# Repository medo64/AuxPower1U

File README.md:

# AuxPower1U

This project is 1U enclosed case with 5 DC outputs that are separately
controllable via front momentary switches with LEDs.

Features:
* 5 DC inputs (input 1 has to be 9-15V)
* 5 DC outputs
* 5 separate button controls
* voltage and current monitoring (9-60V, 0-8A, per channel)
* temperature monitoring
* OLED output
* 3 power supplies
* 2 power inputs (one for UPS, one for non-UPS)

## Usage

Different functionality can be triggered by different key press lengths:
* <5 seconds:    detail mode for channel (turns off automatically in 60 seconds)
* 5-10 seconds:  reset once button is released (or turns on if output was turned off)
* 10-13 seconds: turn off output permanently
* >13 seconds:   ignore press

## Uart Communication

Current usage will be written to UART twice a second. See example below:

    1: 11.98V 0.40A   4.77W [ON]
    2: 15.40V 3.10A  47.74W [ON]
    3: 15.42V 0.00A   0.00W [OFF]
    4: 15.42V 0.00A   0.00W [OFF]
    5: 54.13V 0.00A   0.00W [OFF]
    T: 23.4C

Each line consists of the space-separated readings. If line starts with a
channel number (1-5), what follows will be readings for the given channel of
voltage (V), current (A), and power (W) followed by a channel status. If line
starts with a letter T, what follows is a temperature. Each line will end with
`CRLF`.

Commands can be given to device by sending command code followed by a channel.
Available commands are:
* `D`: Disable
* `E`: Enable
* `R`: Reset
* `I`: Information

For example, to disable channel 2 use:

    D2

### 3.5mm Uart Connector

This is pinout, as viewed from board side (i.e. as marked on board).

| JST | 3.5mm  | Signal |
|-----|--------|--------|
|  1  | Tip    | RX     |
|  2  | Sleeve | GND    |
|  3  | Ring   | TX     |

## Test Mode

To enter test mode, keep buttons 1 and 5 pressed while powering board on. Each
subsequent press will then cycle through channel and show voltage/current values
in higher than normal resolution.

## Components

* [MainController](src/MainController/README.md): Allowing for monitoring and resetting of lines
* [AuxFanController](https://github.com/medo64/AuxFanController): Optional board to run PWM fans dependant on temperature
* [DellPowerTrigger](https://github.com/medo64/DellPowerTrigger): Emulating Dell charger for 5.5x2.1mm input

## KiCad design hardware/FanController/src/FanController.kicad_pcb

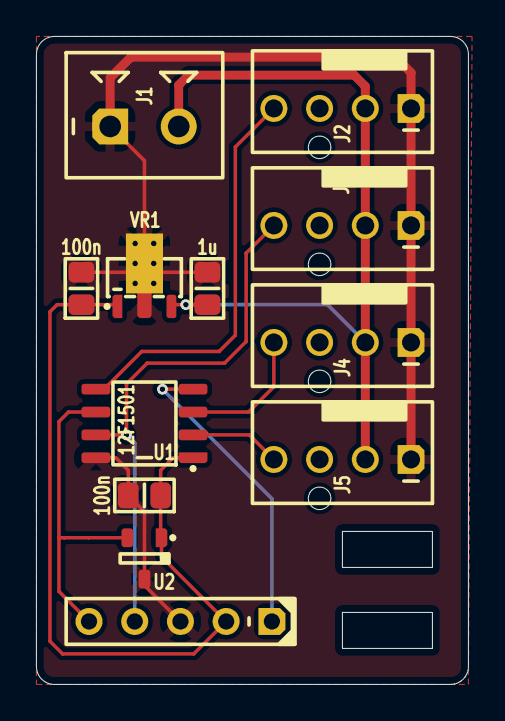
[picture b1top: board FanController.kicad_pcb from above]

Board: 2 copper layers, 24.0 x 36.0 mm, 12 parts (0 on the bottom side), 9 nets.

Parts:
C1, C2: 100n; C (0805)
C3: 1u; C (0805)
ICSP: Microchip PIC; ICSP PIC Pogo (5w)
J1: MC 1,5/2; J Phoenix MCV (2w)
J2, J3, J4, J5: Fan; J Molex 047053 [Fan] (4w)
U1: 12F1501; U Micro [PIC12F1501] (SOIC-8)
U2: MCP9701A; U Temperature Analog [MCP9701] (SOT23-3)
VR1: AS78L05RTR; VR Linear 5V 100mA [AS78L05RTR-E1] (SOT89-3')

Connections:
+5V: C1.1, C2.1, ICSP.2, U1.1, U2.1, VR1.1
+12V: C3.1, J1.2, J2.2, J3.2, J4.2, J5.2, VR1.3
ADC_TEMPERATURE: ICSP.5, U1.6, U2.2
GND: C1.2, C2.2, C3.2, ICSP.3, J1.1, J2.1, J3.1, J4.1, J5.1, U1.8, U2.3, VR1.2
ICSP_VPP: ICSP.1, U1.4
OUT_PWM1: J2.4, U1.5
OUT_PWM2: ICSP.4, J3.4, U1.7
OUT_PWM3: J4.4, U1.3
OUT_PWM4: J5.4, U1.2

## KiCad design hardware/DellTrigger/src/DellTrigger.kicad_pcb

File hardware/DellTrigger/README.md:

# DellTrigger

Small board that allows standard 5.5x2.1 power supply to be used for Dell
Optiplex 3050 Micro.

For the purpose of powering Dell 3050 Micro, one needs to trick computer to
recognize charger correctly. For that purpose, [a simple circuit](https://forum.arcadecontrols.com/index.php?topic=118584.0)
is needed.

Features:
* Allows 5.5x2.1mm DC input
* Has 1-wire control chip (DS2501)
* Dell-compatible 3-pin output

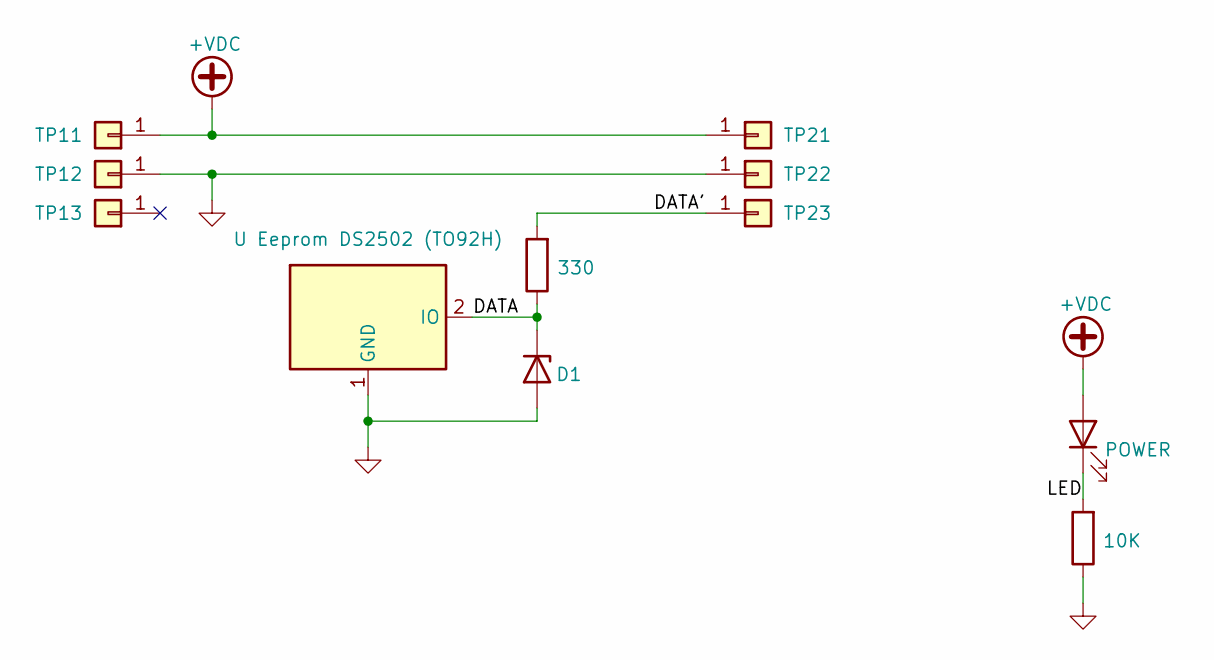
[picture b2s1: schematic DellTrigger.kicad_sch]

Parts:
D1: CUS08F30; D (SOD323)
DS1: POWER; DS (0805)
R1: 330; R (0805)
R2: 10K; R (0805)
TP11, TP21: +; TP Pad (8.0x4.0)
TP12, TP22: -; TP Pad (8.0x4.0)
TP13: S; TP Pad (8.0x4.0)
TP23: D; TP Pad (8.0x4.0)
U1: U Eeprom DS2502 (TO92H)

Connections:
+VDC: DS1.2 (A), TP11.1, TP21.1
DATA: D1.1 (K), R1.1, U1.2 (IO)
DATA': R1.2, TP23.1
GND: D1.2 (A), R2.1, TP12.1, TP22.1, U1.1 (GND)
LED: DS1.1 (K), R2.2

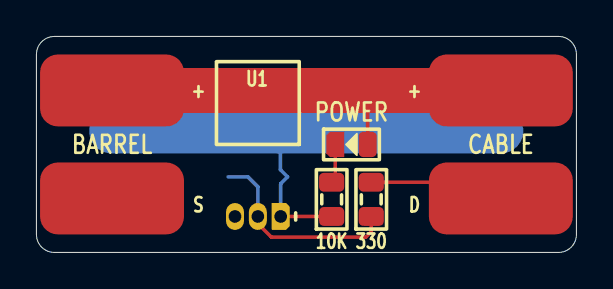
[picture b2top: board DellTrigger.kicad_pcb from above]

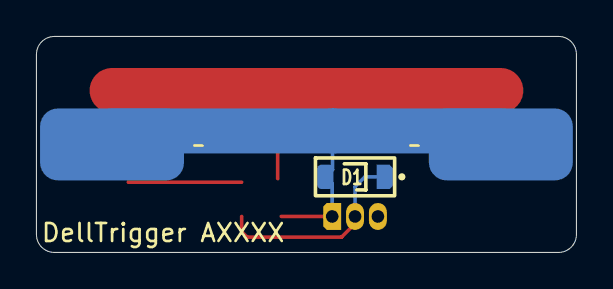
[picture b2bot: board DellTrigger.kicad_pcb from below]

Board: 2 copper layers, 30.0 x 12.0 mm, 11 parts (3 on the bottom side), 5 nets.

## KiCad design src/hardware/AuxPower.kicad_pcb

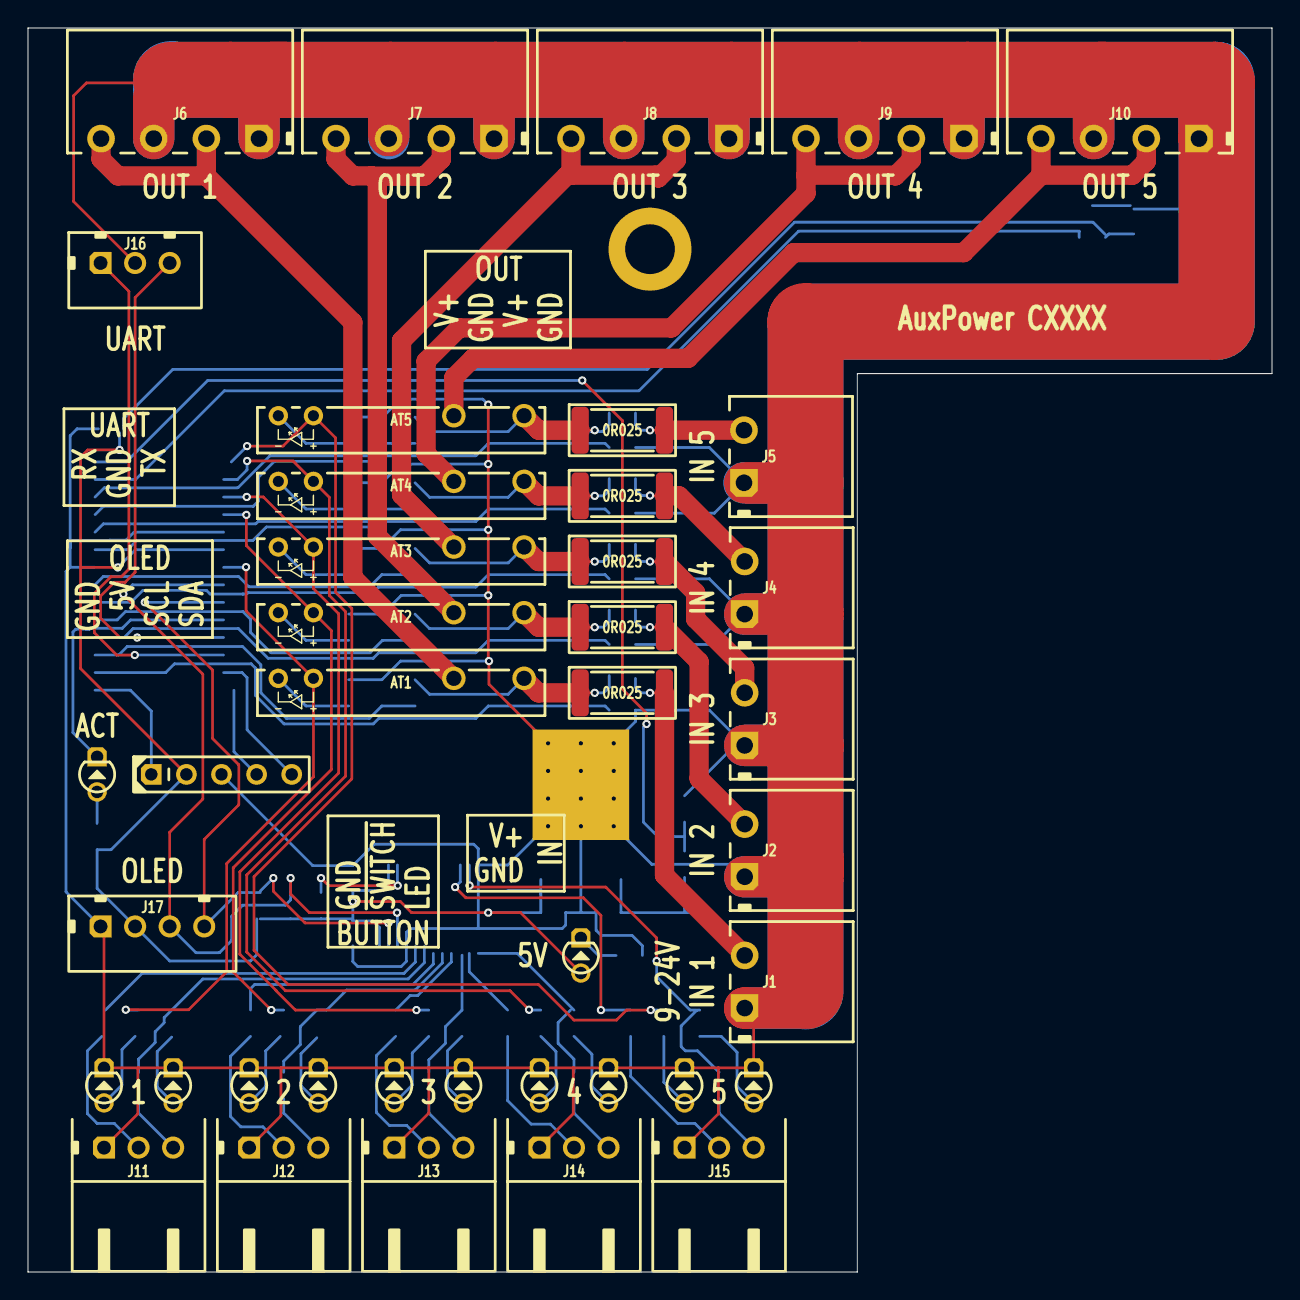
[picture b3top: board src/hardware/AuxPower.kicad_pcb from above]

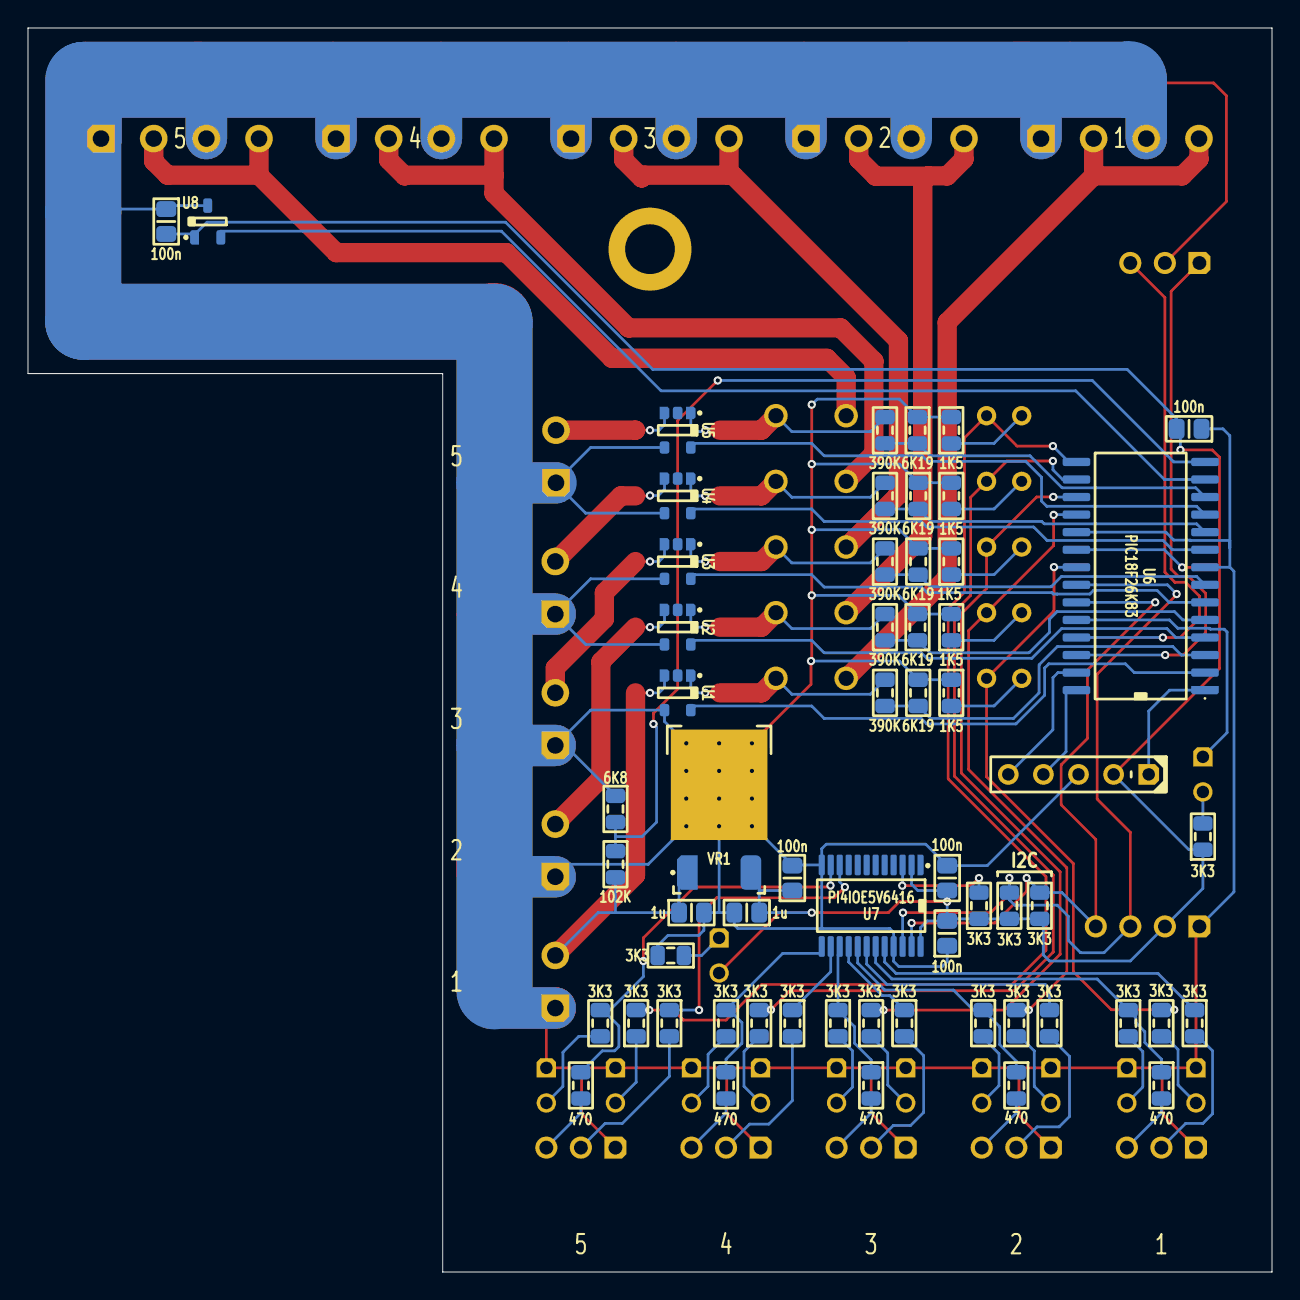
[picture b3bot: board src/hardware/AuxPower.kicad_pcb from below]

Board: 2 copper layers, 90.0 x 90.0 mm, 99 parts (58 on the bottom side), 80 nets.

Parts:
AT1, AT2, AT3, AT4, AT5: AQZ202G; AT PhotoMOS [AQZ202G] (SIP-4)
C1, C2, C3, C4, C5: 100n; C (0805)
C6, C7: 1u; C (0805)
DS1, DS2, DS3, DS4, DS5, DS6, DS7, DS8, DS9, DS10, DS11, DS12: LED; DS (D3.0)
ICSP: Microchip PIC; ICSP PIC Pogo DS (5w)
J1, J2, J3, J4, J5: MC 1,5/2; J Phoenix MC (2w)
J6, J7, J8, J9, J10: MC 1,5/4; J Phoenix MC (4w)
J11, J12, J13, J14, J15: S3B-XH-A; J JST XH S (3w)
J16: B3B-XH-A; J JST XH B [UART] (3w)
J17: B4B-XH-A; J JST XH B [I2C] (4w)
MH1: M3; MH M3
R1, R2, R3, R4, R5: 0R025; R (2512)
R6, R7, R8, R9, R10: 470; R (0805)
R11, R12, R13, R14, R15: 1K5; R (0805)
R16, R17, R18, R19, R20, R21, R22, R23, R24, R25, R26, R27, R28, R29, R30, R31, R32, R33, R34, R35: 3K3; R (0805)
R36, R37, R38, R39, R40: 6K19; R (0805)
R41: 6K8; R (0805)
R42: 102K; R (0805)
R43, R44, R45, R46, R47: 390K; R (0805)
U1, U2, U3, U4, U5: HV7801; U CurrentMonitor [HV7801] (SOT23-5)
U6: PIC18F26K83; U Micro [PIC18F26K83] (SOIC-28)
U7: PI4IOE5V6416; U Expander I2C [PI4IOE5V6416LEX] (TSSOP-24)
U8: MCP9701; U Temperature Analog [MCP9701] (SOT23-3)
VR1: AS7805ADTR; VR Linear 5V 1000mA [AS7805ADTR-G1] (TO252-2')

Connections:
5V: C1.2, C2.1, C3.1, C4.1, C5.1, C6.2, DS11.2, ICSP.2, J17.2, R16.2, R27.2, R34.2, R35.2, U6.20, U7.2, U7.24, U8.1, VR1.3
ADC_CURRENT1: U1.5, U6.2
ADC_CURRENT2: U2.5, U6.4
ADC_CURRENT3: U3.5, U6.6
ADC_CURRENT4: U4.5, U6.9
ADC_CURRENT5: U5.5, U6.11
ADC_TEMPERATURE: U6.13, U8.2
ADC_VOLTAGE1: R36.1, R43.1, U6.3
ADC_VOLTAGE2: R37.1, R44.2, U6.5
ADC_VOLTAGE3: R38.1, R45.2, U6.7
ADC_VOLTAGE4: R39.1, R46.2, U6.10
ADC_VOLTAGE5: R40.1, R47.2, U6.12
ADC_VOLTAGE_IN: R41.1, R42.2, U6.14
BUTTON1_LED: J11.3, R6.1
BUTTON1_SWITCH: J11.2, R29.1
BUTTON2_LED: J12.3, R7.1
BUTTON2_SWITCH: J12.2, R30.1
BUTTON3_LED: J13.3, R8.1
BUTTON3_SWITCH: J13.2, R31.1
BUTTON4_LED: J14.3, R9.1
BUTTON4_SWITCH: J14.2, R32.1
BUTTON5_LED: J15.3, R10.1
BUTTON5_SWITCH: J15.2, R33.1
EXPANDER_RESET: R16.1, U7.3
GND: C1.1, C2.2, C3.2, C4.2, C5.2, C6.1, C7.1, DS1.1, DS2.1, DS3.1, DS4.1, DS5.1, DS6.1, DS7.1, DS8.1, DS9.1, DS10.1, ICSP.3, J1.1, J2.1, J3.1, J4.1, J5.1, J6.1, J6.3, J7.1, J7.3, J8.1, J8.3, J9.1, J9.3, J10.1, J10.3, J11.1, J12.1, J13.1, J14.1, J15.1, J16.2, J17.1, R11.2, R12.1, R13.1, R14.1, R15.1, R26.1, R36.2, R37.2, R38.2, R39.2, R40.2, R41.2, U1.4, U2.4, U3.4, U4.4, U5.4, U6.8, U6.19, U7.12, U7.21, U8.3, VR1.2
I2C_SCL: J17.3, R35.1, U6.22, U7.22
I2C_SDA: J17.4, R34.1, U6.23, U7.23
ICSP_CLK: ICSP.5, U6.27
ICSP_DAT: ICSP.4, U6.28
ICSP_VPP: ICSP.1, U6.1
INPUT1: C7.2, J1.2, R1.1, R42.1, U1.3, VR1.1
INPUT1': AT1.4, R1.2, R43.2, U1.1
INPUT2: J2.2, R2.1, U2.3
INPUT2': AT2.4, R2.2, R44.1, U2.1
INPUT3: J3.2, R3.1, U3.3
INPUT3': AT3.4, R3.2, R45.1, U3.1
INPUT4: J4.2, R4.1, U4.3
INPUT4': AT4.4, R4.2, R46.1, U4.1
INPUT5: J5.2, R5.1, U5.3
INPUT5': AT5.4, R5.2, R47.1, U5.1
IN_BUTTON1_SWITCH: R29.2, U7.20
IN_BUTTON2_SWITCH: R30.2, U7.18
IN_BUTTON3_SWITCH: R31.2, U7.16
IN_BUTTON4_SWITCH: R32.2, U7.14
IN_BUTTON5_SWITCH: R33.2, U7.10
LED_ACTIVITY: DS12.2, R27.1
LED_BUTTON_INT_1: DS1.2, R28.1
LED_BUTTON_INT_2: DS2.2, R22.1
LED_BUTTON_INT_3: DS3.2, R23.1
LED_BUTTON_INT_4: DS4.2, R24.1
LED_BUTTON_INT_5: DS5.2, R25.1
LED_OUTPUT1: DS6.2, R17.2
LED_OUTPUT2: DS7.2, R18.2
LED_OUTPUT3: DS8.2, R19.2
LED_OUTPUT4: DS9.2, R20.2
LED_OUTPUT5: DS10.2, R21.2
LED_POWER: DS11.1, R26.2
OUTPUT1: AT1.3, J6.2, J6.4
OUTPUT2: AT2.3, J7.2, J7.4
OUTPUT3: AT3.3, J8.2, J8.4
OUTPUT4: AT4.3, J9.2, J9.4
OUTPUT5: AT5.3, J10.2, J10.4
OUT_ACTIVITY: DS12.1, U6.24
OUT_BUTTON1_LED: R6.2, R28.2, U7.19
OUT_BUTTON2_LED: R7.2, R22.2, U7.17
OUT_BUTTON3_LED: R8.2, R23.2, U7.15
OUT_BUTTON4_LED: R9.2, R24.2, U7.13
OUT_BUTTON5_LED: R10.2, R25.2, U7.11
OUT_OUTPUT1: AT1.2, R17.1, U6.21
OUT_OUTPUT1': AT1.1, R11.1
OUT_OUTPUT2: AT2.2, R18.1, U6.18
OUT_OUTPUT2': AT2.1, R12.2
OUT_OUTPUT3: AT3.2, R19.1, U6.17
OUT_OUTPUT3': AT3.1, R13.2
OUT_OUTPUT4: AT4.2, R20.1, U6.16
OUT_OUTPUT4': AT4.1, R14.2
OUT_OUTPUT5: AT5.2, R21.1, U6.15
OUT_OUTPUT5': AT5.1, R15.2
UART_RX: J16.1, U6.26
UART_TX: J16.3, U6.25

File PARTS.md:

## AuxPower PCB

### Properties

|      |                            |
|------|----------------------------|
| Size | 90.0 x 90.0 mm ~ 15.2 sqin |


### Parts

|  # | Part name                                          | RefDes   | Source                                                      |
|---:|----------------------------------------------------|----------|-------------------------------------------------------------|
|  5 | AT PhotoMOS 6A 60V [AQZ202G] (SIP-4)               | AT1-AT5  | 255-5699-ND                                                 |
|  5 | C 100nF X7R 50V (0805)                             | C1-c5    | 478-5311-1-ND                                               |
|  2 | C 1uF X7R 25V (0805)                               | C6-C7    | 1276-1066-1-ND                                              |
| 12 | DS LED Red (3mm)                                   | DS1-DS12 | 754-1218-ND                                                 |
|  5 | J Phoenix MC 1,5/ 2-G-3,81 R/A (2w)                | J1-J5    | ED2808-ND                                                   |
|  5 | J Phoenix MC 1,5/ 4-G-3,81 R/A (4w)                | J6-J10   | ED2810-ND                                                   |
|  5 | J JST XH r/a (3w)                                  | J11-J15  | 455-S3B-XH-A-ND                                             |
|  1 | J JST XH (3w)                                      | J16      | 455-2248-ND                                                 |
|  1 | J JST XH (4w)                                      | J17      | 455-B4B-XH-A-ND                                             |
|  5 | R 0.025 1% 3W (2512)                               | R1-R5    | CRA2512-FZ-R025ELFCT-ND                                     |
|  5 | R 470 1% 0.125W (0805)                             | R6-R10   | RMCF0805FT470RCT-ND                                         |
|  5 | R 1.5K 1% 0.125W (0805)                            | R11-R15  | RMCF0805FT1K50CT-ND                                         |
| 20 | R 3.3K 1% 0.125W (0805)                            | R16-R35  | RMCF0805FT3K30CT-ND                                         |
|  5 | R 6.19K 0.1% 0.125W (0805)                         | R36-R40  | P6.19KDACT-ND                                               |
|  1 | R 6.80K 0.1% 0.125W (0805)                         | R41      | P6.8KDACT-ND                                                |
|  1 | R 102K 0.1% 0.125W 1% (0805)                       | R42      | P102KDACT-ND                                                |
|  5 | R 390K 0.1% 0.125W (0805)                          | R43-R47  | P390KDACT-ND                                                |
|  5 | U CurrentMonitor [HV7801] (SOT23-5)                | U1-U5    | HV7801K1-GCT-ND                                             |
|  1 | U Micro [PIC18F26K83] (SOIC-28)                    | U6       | PIC18F26K83-I/SO-ND                                         |
|  1 | U Expander I2C [PI4IOE5V6416LEX] (TSSOP-24)        | U7       | PI4IOE5V6416LEXDICT-ND                                      |
|  1 | U Temperature Analog 2% [MCP9701A] (SOT23-3)       | U8       | MCP9701AT-E/TTCT-ND                                         |
|  1 | VR Linear 5V 1A [AS7805ADTR-G1] (TO252-2)          | VR1      | AS7805ADTR-G1DICT-ND                                        |
|  5 | P Phoenix MC 1,5/ 2-ST-3,81 (2w)                   | P1-P5    | ED2875-ND                                                   |
|  5 | P Phoenix MC 1,5/ 4-ST-3,81 (4w)                   | P6-P10   | ED2877-ND                                                   |


### Pin Usage (PIC18F26K83)

|  # | Pin | ICSP | Function | Description                                |
|---:|:---:|------|----------|--------------------------------------------|
|  1 | RE3 | MCLR |          |                                            |
|  2 | RA0 |      | ANA0     | Out 1: Current (ADC 1.024V 1:5)            |
|  3 | RA1 |      | ANA1     | Out 1: Voltage (ADC 1.024V 16mV/bit; 1:64) |
|  4 | RA2 |      | ANA2     | Out 2: Current (ADC 1.024V 1:5)            |
|  5 | RA3 |      | ANA3     | Out 2: Voltage (ADC 1.024V 16mV/bit; 1:64) |
|  6 | RA4 |      | ANA4     | Out 3: Current (ADC 1.024V 1:5)            |
|  7 | RA5 |      | ANA5     | Out 3: Voltage (ADC 1.024V 16mV/bit; 1:64) |
|  8 | Vss | GND  | -        | -                                          |
|  9 | RA7 |      | ANA7     | Out 4: Current (ADC 1.024V 1:5)            |
| 10 | RA6 |      | ANA6     | Out 4: Voltage (ADC 1.024V 16mV/bit; 1:64) |
| 11 | RC0 |      | ANC0     | Out 5: Current (ADC 1.024V 1:5)            |
| 12 | RC1 |      | ANC1     | Out 5: Voltage (ADC 1.024V 16mV/bit; 1:64) |
| 13 | RC2 |      | ANC2     | Temperature sensor (ADC 2.048V 0.02C/bit)  |
| 14 | RC3 |      | ANC3     | In 1: Voltage  (ADC 1.024V 4mV/bit; 1:16)  |
| 15 | RC4 |      | C4       | Out 5: Control                             |
| 16 | RC5 |      | C5       | Out 4: Control                             |
| 17 | RC6 |      | C6       | Out 3: Control                             |
| 18 | RC7 |      | C7       | Out 2: Control                             |
| 19 | Vss | GND  | -        | -                                          |
| 20 | Vdd | 5V   | -        | -                                          |
| 21 | RB0 |      | B0       | Out 1: Control                             |
| 22 | RB1 |      | I2C SCL  | I2C                                        |
| 23 | RB2 |      | I2C SDA  | I2C                                        |
| 24 | RB3 |      | B3       | LED: Activity                              |
| 25 | RB4 |      | UART TX  | UART                                       |
| 26 | RB5 |      | UART RX  | UART                                       |
| 27 | RB6 | CLK  |          |                                            |
| 28 | RB7 | DAT  |          |                                            |


### Pin Usage (PI4IOE5V6416)

|  # | Pin   | ICSP | Description        |
|---:|:-----:|------|--------------------|
|  1 | INT   |      | -                  |
|  2 | Vdd/I | 5V   | -                  |
|  3 | RESET |      | -                  |
|  4 | P0_0  |      | ~~Out 1: Control~~ |
|  5 | P0_1  |      | ~~Out 2: Control~~ |
|  6 | P0_2  |      | ~~Out 3: Control~~ |
|  7 | P0_3  |      | ~~Out 4: Control~~ |
|  8 | P0_4  |      | ~~Out 5: Control~~ |
|  9 | P0_5  |      |                    |
| 10 | P0_6  |      | Button 5: ~Switch  |
| 11 | P0_7  |      | Button 5: LED      |
| 12 | Vss   | GND  | -                  |
| 13 | P1_0  |      | Button 4: LED      |
| 14 | P1_1  |      | Button 4: ~Switch  |
| 15 | P1_2  |      | Button 3: LED      |
| 16 | P1_3  |      | Button 3: ~Switch  |
| 17 | P1_4  |      | Button 2: LED      |
| 18 | P1_5  |      | Button 2: ~Switch  |
| 19 | P1_6  |      | Button 1: LED      |
| 20 | P1_7  |      | Button 1: ~Switch  |
| 21 | Vss   | GND  | -                  |
| 22 | SCL   |      | I2C SCL            |
| 23 | SDA   |      | I2C SDA            |
| 24 | Vdd/P | 5V   | -                  |

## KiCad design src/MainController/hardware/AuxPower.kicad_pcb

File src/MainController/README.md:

# AuxPower1U: MainController

Features:
* 5 DC inputs (input 1 has to be 9-15V)
* 5 DC outputs
* voltage and current monitoring (9-60V, 0-8A, per channel)
* temperature monitoring
* OLED output

## Usage

Different functionality can be triggered by different key press lengths:
* <5 seconds:    detail mode for channel (turns off automatically in 60 seconds)
* 5-10 seconds:  reset once button is released (or turns on if output was turned off)
* 10-13 seconds: turn off output permanently
* >13 seconds:   ignore press

## Uart Communication

Current usage will be written to UART twice a second. See example below:

    1: 11.98V 0.40A   4.77W [ON]
    2: 15.40V 3.10A  47.74W [ON]
    3: 15.42V 0.00A   0.00W [OFF]
    4: 15.42V 0.00A   0.00W [OFF]
    5: 54.13V 0.00A   0.00W [OFF]
    T: 23.4C

Each line consists of the space-separated readings. If line starts with a
channel number (1-5), what follows will be readings for the given channel of
voltage (V), current (A), and power (W) followed by a channel status. If line
starts with a letter T, what follows is a temperature. Each line will end with
`CRLF`.

Commands can be given to device by sending command code followed by a channel.
Available commands are:
* `D`: Disable
* `E`: Enable
* `R`: Reset
* `I`: Information

For example, to disable channel 2 use:

    D2

### 3.5mm Uart Connector

This is pinout, as viewed from board side (i.e. as marked on board).

| JST | 3.5mm  | Signal |
|-----|--------|--------|
|  1  | Tip    | RX     |
|  2  | Sleeve | GND    |
|  3  | Ring   | TX     |

## Test Mode

To enter test mode, keep buttons 1 and 5 pressed while powering board on. Each
subsequent press will then cycle through channel and show voltage/current values
in higher than normal resolution.

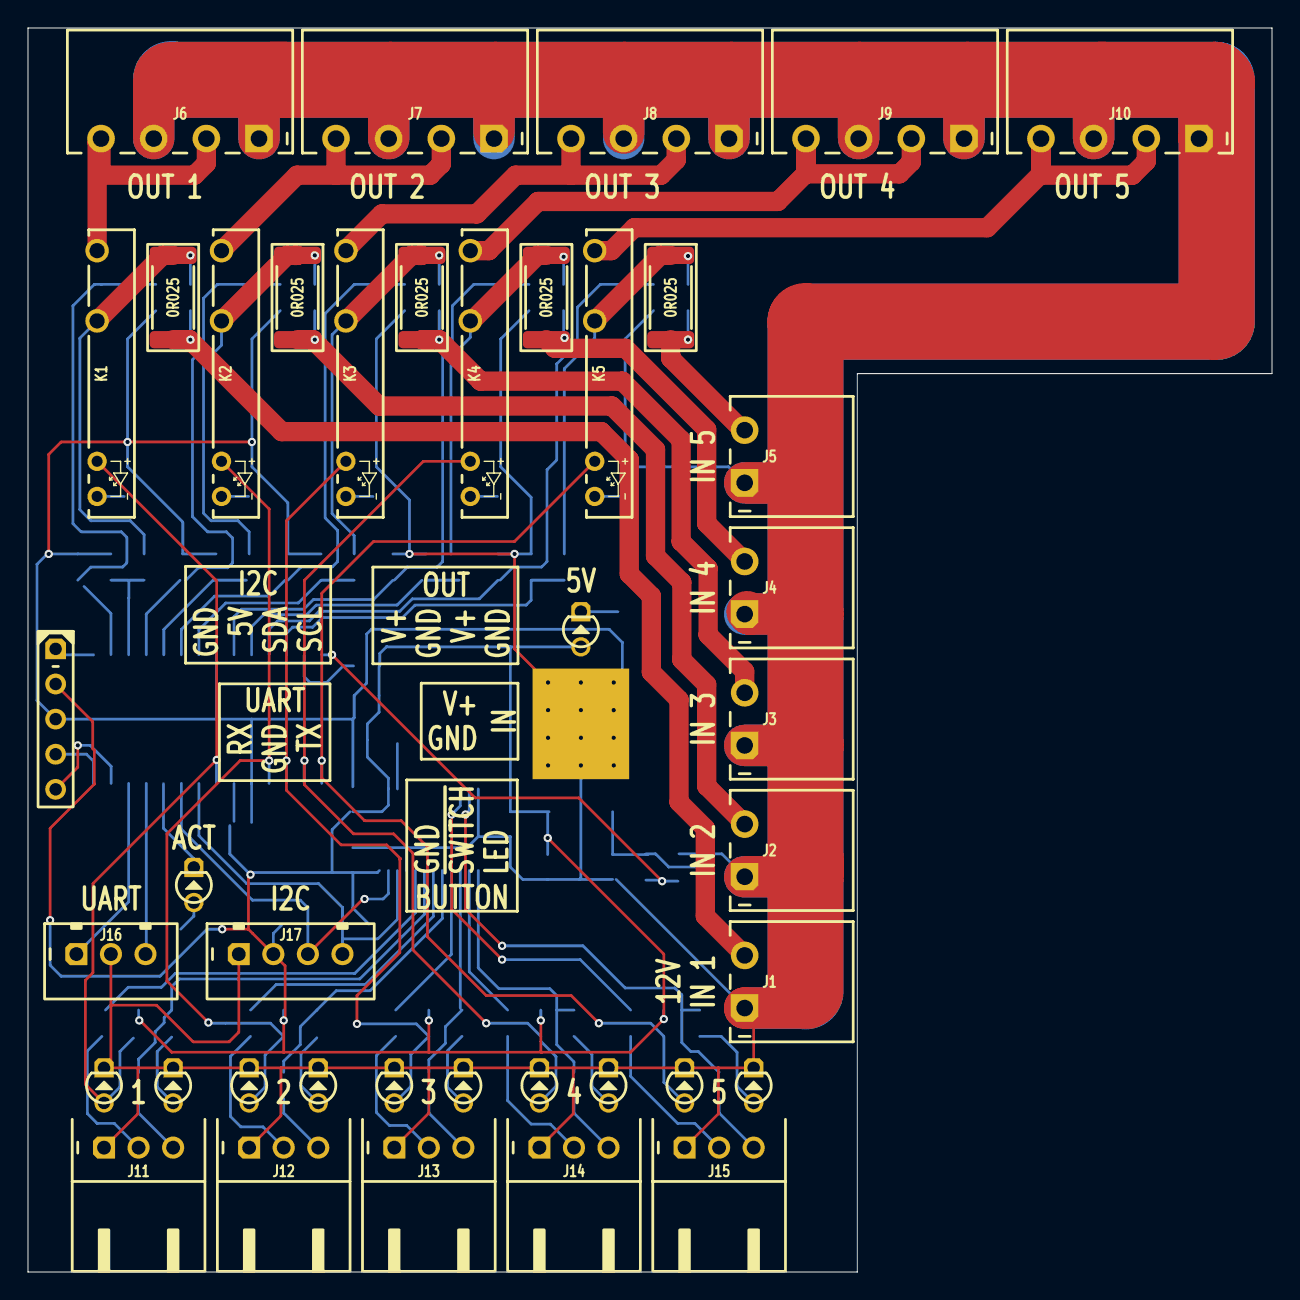
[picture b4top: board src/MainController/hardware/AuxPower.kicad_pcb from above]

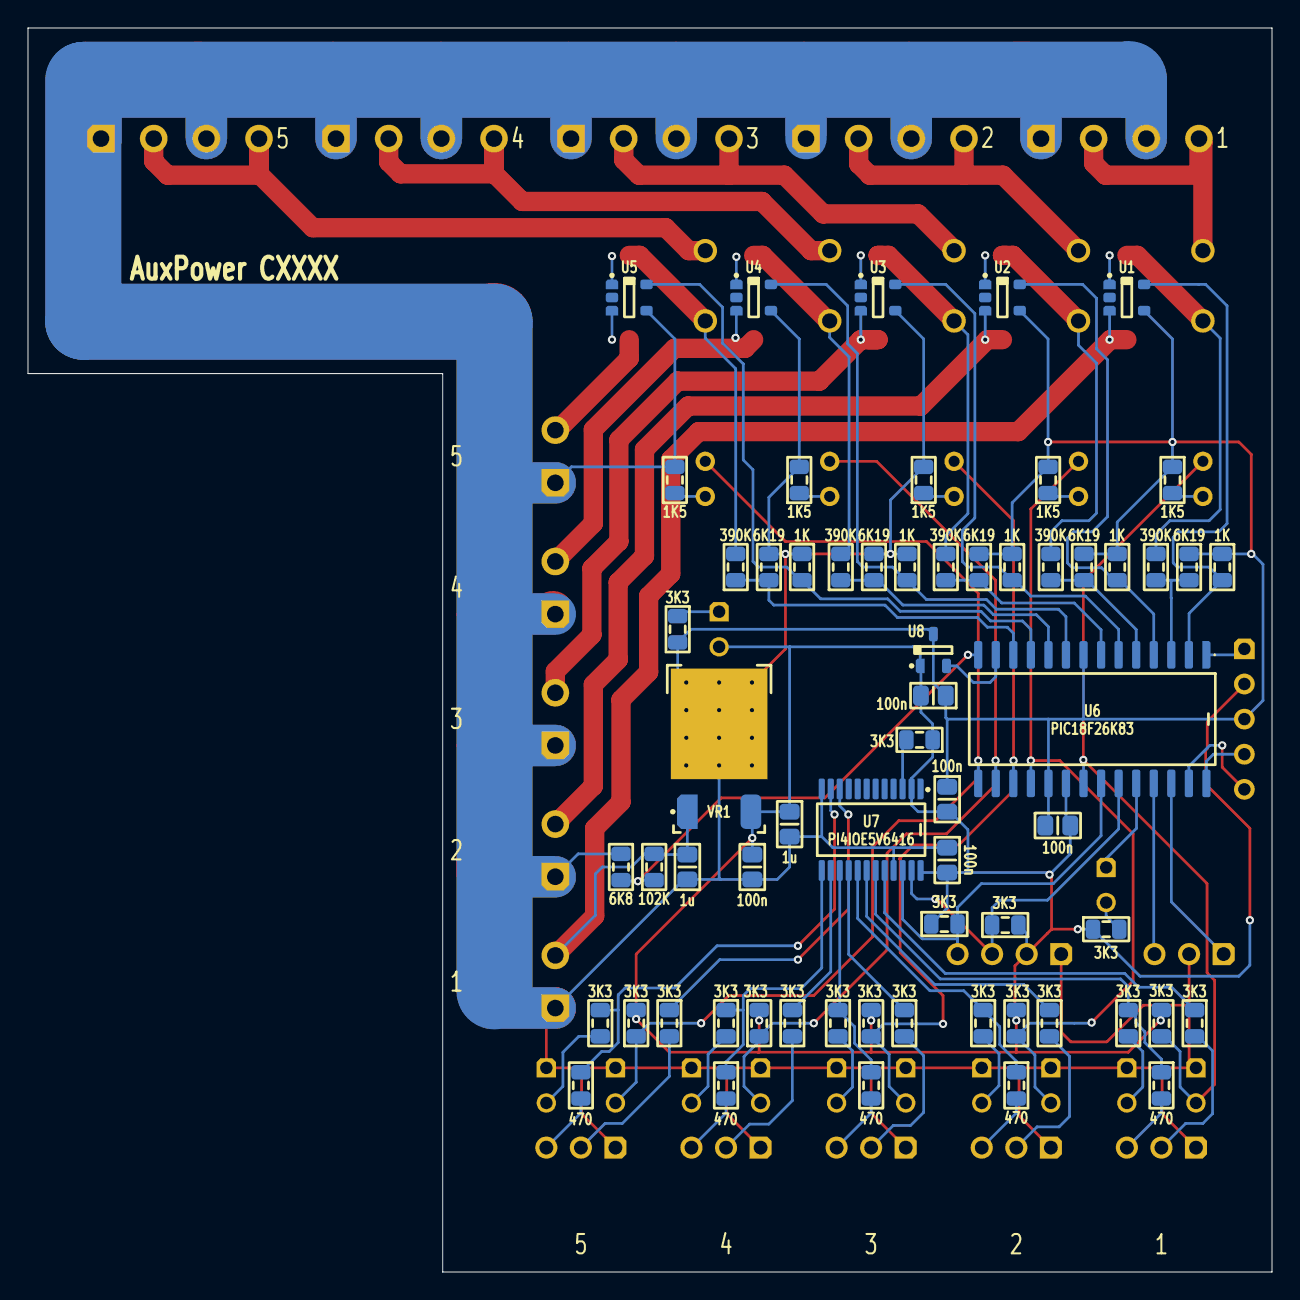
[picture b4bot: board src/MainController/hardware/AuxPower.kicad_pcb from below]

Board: 2 copper layers, 90.0 x 90.0 mm, 103 parts (63 on the bottom side), 75 nets.

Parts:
C1, C2, C3, C4, C5: 100n; C (0805)
C6, C7: 1u; C (0805)
DS1, DS2, DS3, DS4, DS5, DS6, DS7, DS8, DS9, DS10, DS11, DS12: LED; DS (D3.0)
ICSP: Microchip PIC; ICSP PIC Pogo (5w)
J1, J2, J3, J4, J5: MC 1,5/2; J Phoenix MC (2w)
J6, J7, J8, J9, J10: MC 1,5/4; J Phoenix MC (4w)
J11, J12, J13, J14, J15: S3B-XH-A; J JST XH S (3w)
J16: B3B-XH-A; J JST XH B [UART] (3w)
J17: B4B-XH-A; J JST XH B [I2C] (4w)
K1, K2, K3, K4, K5: AQZ202G; K PhotoMOS [AQZ202G] (SIP-4)
R1, R2, R3, R4, R5: 0R025; R (2512)
R6, R7, R8, R9, R10: 470; R (0805)
R11, R12, R13, R14, R15: 1K; R (0805)
R16, R17, R18, R19, R20: 1K5; R (0805)
R21, R22, R23, R24, R25, R26, R27, R28, R29, R30, R31, R32, R33, R34, R35, R36, R37, R38, R39, R40: 3K3; R (0805)
R41, R42, R43, R44, R45: 6K19; R (0805)
R46: 6K8; R (0805)
R47: 102K; R (0805)
R48, R49, R50, R51, R52: 390K; R (0805)
U1, U2, U3, U4, U5: ZXCT1009; U CurrentMonitor [HV7801] (SOT23-5)
U6: PIC18F26K83; U Micro [PIC18F26K83] (SOIC-28)
U7: PI4IOE5V6416; U Expander I2C [PI4IOE5V6416LEX] (TSSOP-24)
U8: MCP9701; U Temperature Analog [MCP9701] (SOT23-3)
VR1: AS7805ADTR; VR Linear 5V 1000mA [AS7805ADTR-G1] (TO252-2')

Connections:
5V: C1.2, C2.1, C3.1, C4.1, C5.1, C6.2, DS11.2, ICSP.2, J17.2, R21.2, R22.1, R23.1, R24.1, R25.1, R26.1, R32.2, R39.2, R40.2, U6.20, U7.2, U7.24, U8.1, VR1.3
ADC_CURRENT1: R11.1, U1.5, U6.2
ADC_CURRENT2: R12.1, U2.5, U6.4
ADC_CURRENT3: R13.1, U3.5, U6.6
ADC_CURRENT4: R14.1, U4.5, U6.9
ADC_CURRENT5: R15.1, U5.5, U6.11
ADC_TEMPERATURE: U6.13, U8.2
ADC_VOLTAGE1: R41.1, R48.1, U6.3
ADC_VOLTAGE2: R42.1, R49.2, U6.5
ADC_VOLTAGE3: R43.1, R50.2, U6.7
ADC_VOLTAGE4: R44.1, R51.2, U6.10
ADC_VOLTAGE5: R45.1, R52.2, U6.12
ADC_VOLTAGE_IN: R46.1, R47.2, U6.14
BUTTON1_LED: J11.3, R6.1
BUTTON1_SWITCH: J11.2, R34.1
BUTTON2_LED: J12.3, R7.1
BUTTON2_SWITCH: J12.2, R35.1
BUTTON3_LED: J13.3, R8.1
BUTTON3_SWITCH: J13.2, R36.1
BUTTON4_LED: J14.3, R9.1
BUTTON4_SWITCH: J14.2, R37.1
BUTTON5_LED: J15.3, R10.1
BUTTON5_SWITCH: J15.2, R38.1
EXPANDER_RESET: R21.1, U7.3
GND: C1.1, C2.2, C3.2, C4.2, C5.2, C6.1, C7.1, DS1.1, DS2.1, DS3.1, DS4.1, DS5.1, DS6.1, DS7.1, DS8.1, DS9.1, DS10.1, ICSP.3, J1.1, J2.1, J3.1, J4.1, J5.1, J6.1, J6.3, J7.1, J7.3, J8.1, J8.3, J9.1, J9.3, J10.1, J10.3, J11.1, J12.1, J13.1, J14.1, J15.1, J16.2, J17.1, R11.2, R12.2, R13.2, R14.2, R15.2, R16.2, R17.1, R18.1, R19.1, R20.1, R31.1, R41.2, R42.2, R43.2, R44.2, R45.2, R46.2, U1.4, U2.4, U3.4, U4.4, U5.4, U6.8, U6.19, U7.12, U7.21, U8.3, VR1.2
I2C_SCL: J17.4, R40.1, U6.22, U7.22
I2C_SDA: J17.3, R39.1, U6.23, U7.23
ICSP_CLK: ICSP.5, U6.27
ICSP_DAT: ICSP.4, U6.28
ICSP_VPP: ICSP.1, U6.1
INPUT1: C7.2, J1.2, R1.1, R47.1, U1.3, VR1.1
INPUT1': K1.3, R1.2, R48.2, U1.1
INPUT2: J2.2, R2.1, U2.3
INPUT2': K2.3, R2.2, R49.1, U2.1
INPUT3: J3.2, R3.1, U3.3
INPUT3': K3.3, R3.2, R50.1, U3.1
INPUT4: J4.2, R4.1, U4.3
INPUT4': K4.3, R4.2, R51.1, U4.1
INPUT5: J5.2, R5.1, U5.3
INPUT5': K5.3, R5.2, R52.1, U5.1
IN_BUTTON1_SWITCH: R34.2, U7.20
IN_BUTTON2_SWITCH: R35.2, U7.18
IN_BUTTON3_SWITCH: R36.2, U7.16
IN_BUTTON4_SWITCH: R37.2, U7.14
IN_BUTTON5_SWITCH: R38.2, U7.10
LED_ACTIVITY: DS12.2, R32.1
LED_BUTTON_INT_1: DS1.2, R33.1
LED_BUTTON_INT_2: DS2.2, R27.1
LED_BUTTON_INT_3: DS3.2, R28.1
LED_BUTTON_INT_4: DS4.2, R29.1
LED_BUTTON_INT_5: DS5.2, R30.1
LED_POWER: DS11.1, R31.2
OUTPUT1: J6.2, J6.4, K1.4
OUTPUT2: J7.2, J7.4, K2.4
OUTPUT3: J8.2, J8.4, K3.4
OUTPUT4: J9.2, J9.4, K4.4
OUTPUT5: J10.2, J10.4, K5.4
OUT_ACTIVITY: DS12.1, U6.24
OUT_BUTTON1_LED: R6.2, R33.2, U7.19
OUT_BUTTON2_LED: R7.2, R27.2, U7.17
OUT_BUTTON3_LED: R8.2, R28.2, U7.15
OUT_BUTTON4_LED: R9.2, R29.2, U7.13
OUT_BUTTON5_LED: R10.2, R30.2, U7.11
OUT_OUTPUT1: DS6.2, K1.2, R22.2, U6.21
OUT_OUTPUT1': K1.1, R16.1
OUT_OUTPUT2: DS7.2, K2.2, R23.2, U6.18
OUT_OUTPUT2': K2.1, R17.2
OUT_OUTPUT3: DS8.2, K3.2, R24.2, U6.17
OUT_OUTPUT3': K3.1, R18.2
OUT_OUTPUT4: DS9.2, K4.2, R25.2, U6.16
OUT_OUTPUT4': K4.1, R19.2
OUT_OUTPUT5: DS10.2, K5.2, R26.2, U6.15
OUT_OUTPUT5': K5.1, R20.2
UART_RX: J16.1, U6.26
UART_TX: J16.3, U6.25
